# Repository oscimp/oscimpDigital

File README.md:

# oscimpDigital
OscillatorIMP ecosystem originally designed for the digital characterization of ultrastable
oscillators, provides most frontend processing blocks for Software Defined Radio (SDR) reception.

## Motivation

This ecosystem aims at providing a consistent software/hardware, chip independent
(Xilinx Zynq, Altera/Intel Cyclone V soc, ... including the 
[Redpitaya STEMlab 125-14](https://redpitaya.com/stemlab-125-14) and
[Redpitaya SDRlab 122-16](https://www.redpitaya.com/p52/sdrlab-122-16-standard-kit) and
[Redpitaya SIGNALlab 250-12](https://redpitaya.com/signallab-250-12) boards) solution, to assemble and build
designs targeted for FPGA and to generate and cross-compile software, running
on the CPU running embedded GNU/Linux, dedicated to communicate/configure
logic parts. The highlights of oscimpDigital were presented at the [European GNU Radio Days 2019](https://youtu.be/fQgIJl7vu2s), [Maker Space conference](https://www.youtube.com/watch?v=SSzR_pnZnjs&feature=youtu.be) in 2019 and [FOSDEM](https://fosdem.org/2020/schedule/event/fsr_platform_independent_cpu_fpga_co_design/) in 2020.

The assumption underlying all IP block design is a pipelined stream of data 
processed at each clock cycle, with no latencies introduced by FIFOs between blocks.

The tree structure of the project aims at clearly separating the FPGA IPs, Linux kernel modules, userspace libraries 
and documentation:

## Versions

As all opensource software that keeps on evolving, tight API constraints require using specific software versions. We aim at
keeping up to date with latest revisions, so that older versions might/will fail. This set of specifications might help debug failures
to setup OscimpDigital:
* Linux kernel >= 6 MUST be used (GPIO indices starting at 512 and not 906)
* Buildroot >= 2024 MUST be used (REMI web server API)
* Vivado 2019 or 2021 (but 2022.2 is failing at the moment)

## Install

This repository is composed of multiple associated submodules (see sub-READMEs
to see each repository goal). Please refer to the [Wiki](https://github.com/oscimp/oscimpDigital/wiki) for pre-requisites and most significantly Buildroot. Vendor specific tools for synthetizing for the targeted FPGA are also assumed to be functional and accessible through the PATH. A **detailed description** of the installation steps for various boards
is available at [the Wiki page](https://github.com/oscimp/oscimpDigital/wiki). The case of the Redpitaya STEM 125-14 is
detailed at the bottom of the page.

Software versions: OscimpDigital relies on Buildroot and Vivado. The version of Buildroot should not matter much 
*except* for the REMI web server whose API keeps on changing: the latest tested version of Buildroot is 2024.11.1
while earlier versions might rely on the old REMI API.

Vivado 2019 and 2021 are regularly used with OscimpDigital.

### Download

To download this repository and submodules in one command, you need to use
```bash
git clone --recursive https://github.com/oscimp/oscimpDigital.git
```

Or
```bash
git clone https://github.com/oscimp/oscimpDigital.git
cd oscimpDigital
git submodule init
git submodule update
```
to 1/ clone oscimpDigital and 2/ add submodule contents.

### Update

To update repositories you need to use
```bash
git pull
git submodule update
```

## Software environnement

Current Vivado version: 2018.2 to 2019.2

Software parts (applications, libraries and drivers), based on a set of
*Makefile*, uses [buildroot](http://www.buildroot.org) to cross-compiles code.

Thus, you need to download, build and flash your board with a *buildroot*
version configured to your target hardware.

For the specific case of the *Redpitaya* board, not officially supported by
*buildroot*, see
[red_readme](https://github.com/trabucayre/redpitaya/blob/master/README.md)

For the specific case of the *PlutoSDR* board, not officially supported by 
*buildroot*, see [plutosdr_readme](https://github.com/oscimp/PlutoSDR/blob/master/README.md)

## Configuration

The OscillatorIMP ecosystem uses shell environment variables to locate each
repository (*lib*, *fpga_ip*, *linux_driver* and *app*) to allow
In or Out Tree access. In addition to these variables, two other variables are
mandatory to know the target board and the *buildroot* root absolute path for
cross-compilation. 

A sample script (*settings.sh.sample*) is proposed as reference to provide a
complete variable set. You must copy this file and adapt its content to your
specific case, mainly filling the fields:
- *BOARD_NAME*: with the name of your board (*redpitaya*, *redpitaya16*, *plutosdr*, *de0nanosoc* *zedboard* as described in the comment at the beginning of the configuration file). This
variable will be used to determine subdirectories of NFS root, to build designs and run Makefiles accordingly.
- *BR_DIR*: with the absolute path of your *buildroot*. this information is
mandatory to have access to the cross-compiler, linux tree and some other
applications. See above the Software environnement section on how to install buildroot if needed.
- *OSCIMP_DIGITAL_NFS* (optional): when you use *make install* for a Linux driver
or an application, files are copied to a sub-directory of *$OSCIMP_DIGITAL_NFS/$BOARD_NAME*.
By default *OSCIMP_DIGITAL_NFS=/nfs*. Change this variable if you want to
install files in other location.

Once this file has been filled and named *settings.sh*, the command:
```bash
source /somewhere/settings.sh
```
will add these variables to the current environment.

**Warning**: the previous command will add variables only to the current
terminal. To make this setting permanent, the script sourcing must be added
in the user's *~/.bashrc*.

## How it compares with existing solutions ?

Various FPGA design frameworks have been available. Here we list the reasons for pursuing this particular approach of close FPGA/Linux module/GNULinux userspace codesign with respect to other approaches:
- the proprietary approach: of course Xilinx (Vivado) & Altera/Intel (Quartus) provide ready made blackbox solutions to FPGA programming. If you want a vendor-locked solution, these are probably the best alternatives. We want to invest in vendor independent solution that will allow to deploy the framework on any field programmable gate arrays, whether from current (Xilinx/Altera-Intel/Lattice-Microsemi) or future vendors
- Ettus Research has developed RFNOC, an excellent tool for their board but hardly portable to any other platform. A fixed bitstream allows routing packets amongst a fixed set of IPs, as opposed to the proposed approach of a close co-design between the IPs needed for a given design and the associated Linux tools (kernel space and userspace) generated for each new design.
- HLS (High-level Language Synthesis): at the moment most HLS designs require FIFOs and are not compatible with high throughput
streaming data processing, as considered in the radiofrequency data processing for software defined radio
- Migen/Mikymist/ARTIQ (M-Lab)

## [Getting started](https://github.com/oscimp/oscimpDigital/wiki/0Getting-started)

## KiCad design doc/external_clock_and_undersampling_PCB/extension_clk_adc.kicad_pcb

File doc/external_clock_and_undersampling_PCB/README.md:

### PCB for reliable conexion of an external clock and direct connection to ADC inputs for undersampling

Hardware modifications of the 14-bit Red Pitaya (also known as STEMlab 125-14) described
in report.pdf, and the associated KiCAD files (courtesy of Gilles Martin, FEMTO-ST, France,
translated from Eagle) for undersampling by getting rid of the unbalanced-balanced amplifier 
also acting as low pass filter. 

For external clocking (125 MHz), only populate the balun and channel closest to the border of the PCB. The
other two channels are for undersampling by bypassing the unbalanced to balanced differential
amplifiers. Follow
[these instructions](https://redpitaya.readthedocs.io/en/latest/developerGuide/hardware/125-14/top.html#external-125-14)
for wiring modifications (two resistors to be flipped) to disconnect the quartz crystal oscillator
and connect the clock input to the PCLK external source pins.

Replacing the active amplifier with a broadband balun (tested over the whole track-and-hold 
range up to 875 MHz input frequency) requires soldering three tiny wires (differential pair and Vref) 
on each channel at your own risks after removing the inductors connecting the differential 
amplifier output to the ADC inputs. The Vref signal trace must be cut before soldering a 
wire to the via pad whose varnish will have been removed with a sharp blade.

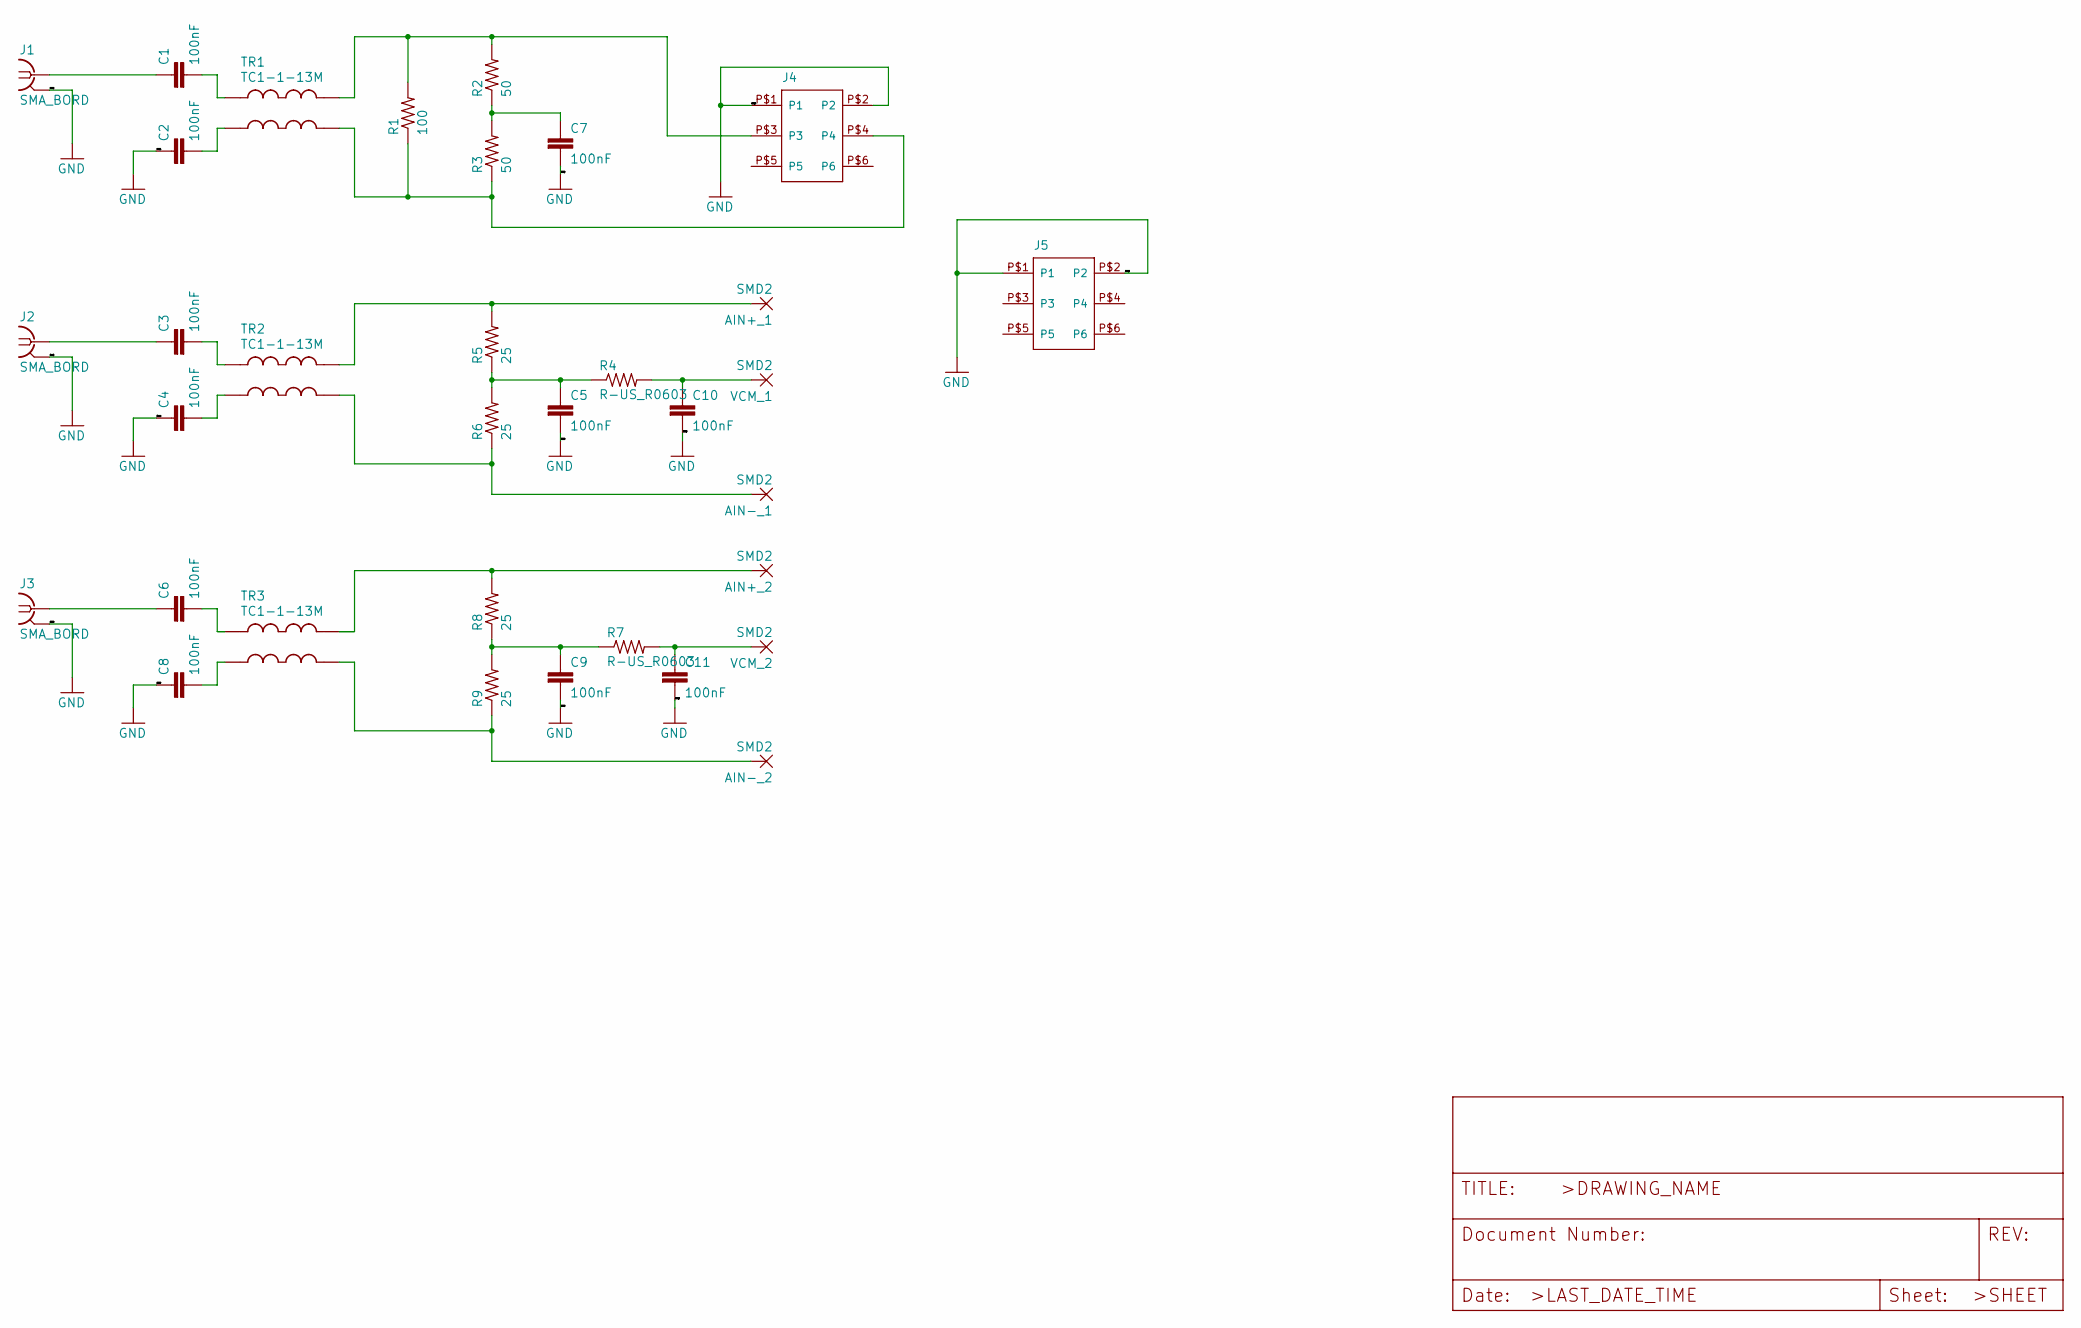
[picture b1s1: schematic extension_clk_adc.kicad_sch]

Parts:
AIN+_1, AIN+_2: SMD2; SMD1,27-2,54
AIN-_1, AIN-_2: SMD2; SMD1,27-2,54
C1, C2, C3, C4, C5, C6, C8, C9, C10, C11: 100nF; C0402
C7: 100nF; C0603
J1, J2, J3: SMA_BORD
J4, J5: DBL_6; DBL6
R1: 100; R0603
R2, R3: 50; R0603
R4, R7: R-US_R0603; R0603
R5, R6, R8, R9: 25; R0603
TR1, TR2, TR3: TC1-1-13M; AT224-1A
VCM_1, VCM_2: SMD2; SMD1,27-2,54

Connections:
GND: C2.1, C4.1, C5.2, C7.2, C8.1, C9.2, C10.2, C11.2, J1.G@1 (2), J1.G@2 (2), J1.G@3 (2), J1.G@4 (2), J2.G@1 (2), J2.G@2 (2), J2.G@3 (2), J2.G@4 (2), J3.G@1 (2), J3.G@2 (2), J3.G@3 (2), J3.G@4 (2), J4.P$1 (P1), J4.P$2 (P2), J5.P$1 (P1), J5.P$2 (P2)
unnamed: AIN+_1.1, R5.2, TR2.P$3 (SEC)
unnamed: AIN+_2.1, R8.2, TR3.P$3 (SEC)
unnamed: AIN-_1.1, R6.1, TR2.P$1 (SEC_DOT)
unnamed: AIN-_2.1, R9.1, TR3.P$1 (SEC_DOT)
unnamed: C1.1, J1.1
unnamed: C1.2, TR1.P$4 (PR)
unnamed: C2.2, TR1.P$6 (PR_DOT)
unnamed: C3.1, J2.1
unnamed: C3.2, TR2.P$4 (PR)
unnamed: C4.2, TR2.P$6 (PR_DOT)
unnamed: C5.1, R4.1, R5.1, R6.2
unnamed: C6.1, J3.1
unnamed: C6.2, TR3.P$4 (PR)
unnamed: C7.1, R2.1, R3.2
unnamed: C8.2, TR3.P$6 (PR_DOT)
unnamed: C9.1, R7.1, R8.1, R9.2
unnamed: C10.1, R4.2, VCM_1.1
unnamed: C11.1, R7.2, VCM_2.1
unnamed: J4.P$3 (P3), R1.2, R2.2, TR1.P$3 (SEC)
unnamed: J4.P$4 (P4), R1.1, R3.1, TR1.P$1 (SEC_DOT)

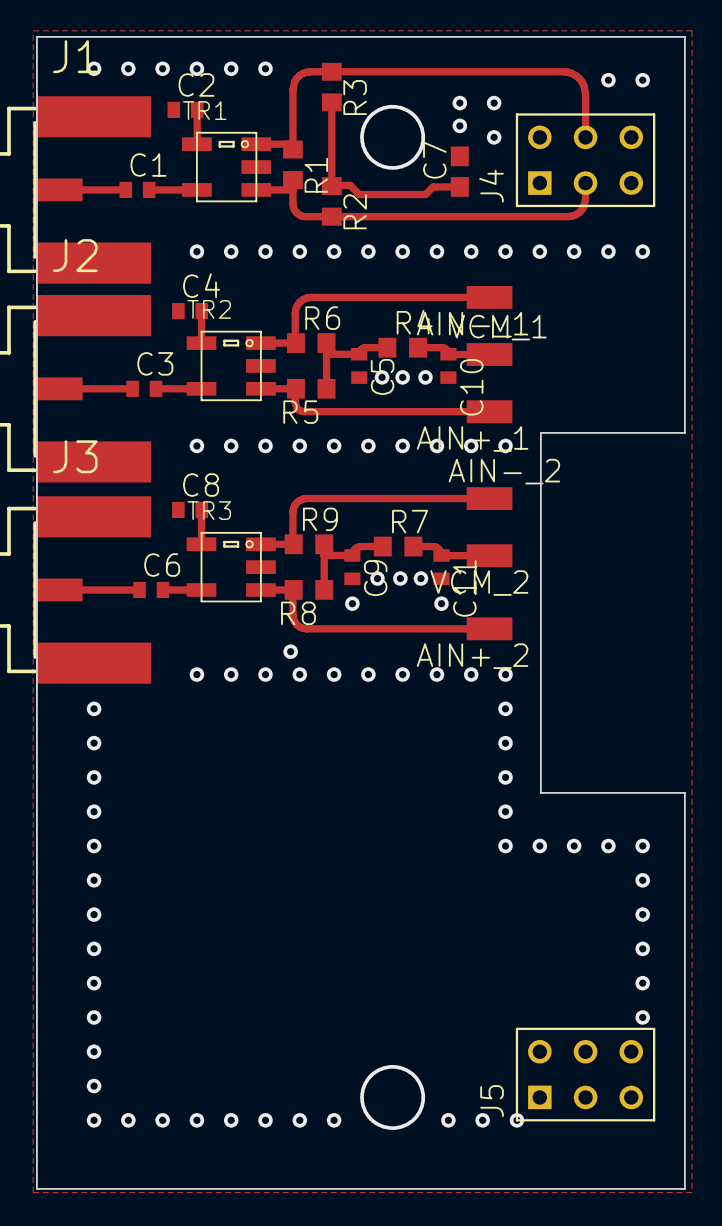
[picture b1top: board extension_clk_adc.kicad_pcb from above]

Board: 2 copper layers, 36.0 x 64.0 mm, 34 parts (0 on the bottom side), 21 nets.

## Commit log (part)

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2019-03-07 update fpga_ip ref: dataComplex, dataReal, nco: improve clock domain communication. dataReal, dataComplex: set axi busy reg high ASAP
2019-03-07 update fpga_ip ref: minor update for nco_counter
2019-03-20 fpga_ip: axiStreamToComplex, axiStreamToReal
2019-03-20 app: module_generator: minor fix
2019-04-01 README
2019-04-02 clock domain error corrected => new datasets and figure
2019-04-02 corrected documentation
2019-04-13 header file
2019-04-19 update linux_driver ref: - add_const to communicate with add_constXX IPs - axi_to_dac to communicate with axi_to_dac
2019-04-19 update lib ref: - add_const: wrapper for add_const_core driver and add_constXX IPs
2019-05-20 update fpga_ip ref: prn: pseudo random number generator xcorr_gps_slow_complex: xcorr between one data stream and one 1bit prn
2019-05-30 update linux_driver ref: fix build for axi_to_dac
2019-06-01 update fpga_ip: new dfu_frm.mk to build flash files out of buildroot
2019-06-04 app: - module_generator: WA for plutosdr - Makefile.inc: add rule to install by ssh
2019-06-06 update fpga_ip ref
2019-06-09 cleanup tutorial3
2019-06-15 doc:tutorials:plutosdr:1-adalmPluto_within_OscimpDigital: add project1 design and app
2019-06-15 update app ref: module_generator minor update
2019-06-15 settings.sh.sample: add details about BOARD_NAME, IP var and ADI_HDL_DIR for plutosdr board
2019-06-16 ignore: add vivado output directory
2019-06-16 update fpga_ip ref: axiStreamToComplex minor update
2019-06-16 doc/tutorials/plutosdr/1-adalmPluto_within_OscimpDigital/project2: TCL based with NCO/demod
2019-06-18 2-PRN_on_PL: update designs
2019-06-18 update app ref: add default design for plutosdr withoscimpDigital support
2019-07-18 doc:IP: add shifter description
2019-07-25 fpga_ip update: new: - shifterReal_dyn,shifterComplex_dyn - redpitaya16 preset - redpitaya_converters - realToAxiStream update: - ip.xml - axi_to_dac
2019-07-25 update lib: new: - utils_conf with shifterXXX_dyn support - axi_to_dac_conf update: - switch,fpgagen: suppress some printf - nco_conf: use 64bits variables and add function to deal with reset accumul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
2019-07-25 update app ref: allows to provides extra files
2019-10-11 doc:IP: add real(complex)ToAxiStream and axiStreamToReal(Complex)
2019-10-16 doc:IP: add documentation about mixerxxx_sin
2019-11-21 slides for the presentation SDR Makerspace (Nov 2019)
2019-11-21 slides
2019-11-24 makerspace: typo
2019-11-29 conference directory
2019-11-29 still conferences ...
2019-11-29 add block assumption
2019-12-19 Redpitaya tutorial: transition to the single ADC/DAC block
2019-12-19 Redpitaya tutorial: transition to the single ADC/DAC block: figure
2019-12-19 Redpitaya tutorial 3: combined ADC/DAC
2019-12-19 Redpitaya tutorial2: xdc full names
2019-12-19 Redpitaya tutorial 2: PDF update
2019-12-19 Redpitaya tutorial2: add shifter between ADC & DAC in case of 16-bit Redpitaya
2019-12-23 Update axi_to_dac.md
    axi_to_dac example: syntax errors
2019-12-23 Redpitaya tutorial 2: correct screenshot for part selection
2019-12-30 Update README.md
    video Makerspace
2020-01-06 Redpitaya tutorial corrections
2020-01-07 Update fpga_ip ref: - new makefile structure with a top generic top makefile and sub .mk used to support commercial tools; - TCL script to provides vendor abstraction layer for design assembly
2020-01-08 fpga_ip: small modification in gen_module_generator_xml
2020-01-08 fpga_ip: minor fix in gen_module_generator_xml
2020-01-08 Revert "doc:IP: axi_to_dac: typo in register REG_DATAB"
    This reverts commit 148972dcdde75082e37f1bfdab2f812007278620.
2020-01-08 tutorials:redpitaya:4-PLPS: update tcl to use redpitaya_converters, add support for redpitaya16 and everything around xml to use current module_generator file content
2020-01-08 tutorials:redpitaya:2-PL: uses redpitaya_converters and add redpitaya16 support
2020-01-09 IP:mixer*
2020-01-11 doc/IP: switch
2020-01-12 doc/IP: data_to_RAM
2020-01-12 doc/redpitaya/4-FIR: FIR tutorial including oscilloscope observation of filtered output
2020-01-12 fpga_ip
2020-01-14 update fpga_ip: - update README - fix boards.def (typo for redpitaya16) - fix FREQ_HZ for redpitaya_converters/clk_o
2020-01-15 doc:tutorials:redpitaya:4-FIR: update design
2020-01-22 update fpga_ip: fix in nco_counter
2020-01-23 update fpga_ip - use coherent parameters name for meanXX - syncTrigStream: produces data stream only on a trigger event - dataComplex_dma_direct: use CPU RAM to store an complex data stream
2020-01-23 doc/IP/nco_counter correction
2020-01-24 update fpga_ip: meanReal small typo
2020-01-24 redpitaya/4-FIR: figure updates
2020-01-27 doc/redpitaya/4-FIR: PDF
2020-01-28 fpga_ip: introduce print_businterfaces: a tools to display IP details
2020-02-03 update fpga_ip
2020-02-05 doc:tutorials:plutosdr:2-PRN_on_PL: prn -> prnGenerator
2020-02-11 doc:tutorials:plutosdr: fix some IP names or parameters
2020-02-13 fpga_ip: minor fix
2020-02-16 Update README.md
    FOSDEM
2020-02-16 cleanup for wiki page
2020-02-16 figure pour wiki
2020-02-18 doc/tutorials/redpitaya/3: be more coherent
2020-02-18 doc/tutorials/redpitaya/4: add missing figure
2020-02-19 settings.sh: add LANG for Vivado to work on French computers
2020-02-27 app with Redpitaya balun circuit
2020-03-03 fpga_ip: ip.xml update
2020-03-03 introduce dupplReal and dupplComplex
2020-03-10 initial draft for TCL tutorial
2020-03-11 Update settings.sh.sample
    board names in settings.sh configuration file
2020-03-11 Update settings.sh.sample
    add PATH to access tools in app (module_generator) and fpga_ip (python script describing IP interfaces)
2020-03-20 update fpga_ip ref: - add pidv3_axi IP - update and fix pwm_axi
2020-03-27 fix app hash
2020-04-21 Create README.md
    documentation creation
2020-04-21 linux_driver: README on how to compile module
2020-04-24 2PL: figure path update
2020-04-24 3-PLPS: README & figure
2020-04-24 3-PLPS: missing figure
2020-04-24 4-FIR: figures
2020-04-24 5-NCO: README & figures
2020-04-24 6_TCL: README & figures
2020-05-09 README.md of webserver_generator
2020-05-09 Tutorial for a first setup with RedPitaya STEM 125-14
2020-05-15 Update main.cpp
    typo
2020-05-15 Doc: move getting started to doc
2020-05-30 add missing pidv3_axi_conf.* files
2020-06-19 move getting started doc associated install* images to doc folder
2020-06-23 Update README.md
    Update to README after merging Redpitaya introductory tutorial with Wiki pages.
2020-06-23 doc/IP: typo
2020-06-24 doc/tutorials/redpitaya/2-PL: resize first fig
2020-06-26 Update axi_to_dac.md
    testing from shell (devmem)
2020-06-30 Update README.md
    Wiki URL
2020-09-27 add example and board name for redpitaya12
2020-09-28 move figure
2020-09-28 webserver_generator update
2020-09-29 declaration of interrupt in dataReal_to_ram
2020-09-29 fpga_ip/dataReal_to_ram: minor fix
2020-09-29 zedboard support
2020-10-02 update redpitaya12 example and IP naming
2020-10-05 update description for redpitaya_converters_12
2020-10-09 example design double_iq_pid_vco for redpitaya12
2020-10-12 fix data_to_ram driver
2020-10-19 Buttons for redpidaya_converters_12 commutators in webserver_generator
2020-10-20 rm useless comments in ip redpitaya_converters_12
2020-10-20 update redpitaya_converters_12 doc
2020-10-20 webserver_generator small errors correction
2020-10-28 redpitaya_converters_12 correct DAC output sign
2020-12-10 Update README.md
    readme: url of conferences describing OscimpDigital
2021-01-06 fpga_ip: small Makefiles update
2021-01-11 app: redpitaya16 support for redpitaya/adcChanADmaDirect
2021-01-11 update app
2021-01-15 fpga_ip: magnitude, cplx_conj
2021-01-19 app/redpitaya/double_iq_pid_vco: redpitaya16 compatibility: WIP
2021-01-27 app: redpitaya/double_iq_pid_vco: WIP
2021-01-28 double_iq_pid_vco diagram
2021-01-29 screenshot
2021-01-29 replace string with boolean, slider callback function with onchange.do, remove UTF8 encoding
2021-02-02 liboscimp_fpga.py correction on get_values
2021-02-04 doc/tutorials/redpitaya/3-PLPS: fix module_generator path
2021-02-04 app:module_generator: more check
2021-02-12 fpga_ip: vivado typo
2021-02-18 lib/pidv3_axi_conf: typo
2021-03-03 Update README.md
    correction and minor changes of the tutorial
2021-03-05 16bit redpitaya procedure paragraph moved up
    the procedure to adapt the code for redpitaya 16 was located at the bottom of the tuto. Now it is located in the connecting blocks to the FPGA so that people will be aware that they can't use the sam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
2021-03-05 adding one step to configure the program for RP16
    to make the program work under redpitaya16, one must check that the redpitaya IP is correctly configured
2021-03-05 Correction amelioration
    more details on some sections
2021-03-05 added comment in the octave program
2021-03-09 pidv3 setpoint is working now
2021-03-18 correction of a minor error
2021-04-02 minor change
2021-04-06 amelioration and correction
2021-04-12 app: tools/webserver_generator: add missing shifterComplex_dyn
2021-04-13 lib: typo
2021-04-14 doc/IP/figures: pidv3 RTL diagram
2021-04-16 fpga_ip: add_const: fix
2021-04-30 fpga_ip: new IP: delayTempoReal_axi
2021-04-30 lib: add delayTempo support
2021-05-03 fpga_ip: new cordicAtan IP
2021-05-11 fix fpga_ip ref'
2021-05-12 fpga_ip/mixerXXX_sin: allows to select primary stream
2021-05-18 add fft ip/lib/driver
2021-05-18 fft in ip.xmp + readme update
2021-05-19 delayTempoReal_axi in webserver_generator
2021-05-28 add window IP
2021-05-28 fpga_ip/README.md + liboscimp_fpga.py
2021-05-28 update fpga_ip/README.md again
2021-06-11 autorun_generator -> be lazy + webserver_generator switchComplex
2021-06-11 add autorun_generator readme
2021-07-02 doc:ip:windowReal: minor corrections
2021-07-14 update window and fft doc
2021-07-15 fft doc with the figure is better
2021-07-15 update app ref
2021-07-16 update readme autorun_generator
2021-07-26 nco in webserver_fenerator: fix float load error
2021-09-07 fpga_ip: fix pidv3 with out size gt internal size
2021-09-08 fpga_ip: nco_counter fix
2021-11-19 update double_iq_pid_vco
2022-03-18 added documentation images for dynamic shifter, iir_lpf_real. For unwrap_phase_diff- after adding the synchronization registers improving the timing performance during Vivado synthesis
2022-03-18 description of IIR lowpass filter
2022-03-31 cropped borders
2022-05-05 fix webserver and remi checkbox value and pluto dfu flash routine
2022-05-05 switch: default to False (as IP)
2022-06-29 fix tab
2022-09-07 now can joint max7311 with both SignalLab v1.1 and v1.2
2022-09-07 rm useless lines
2022-11-21 update lib ref (scp protocol)
2022-11-25 doc/IP: magnitude
2022-11-25 update fpga_ip ref: magnitude and add_const update
2022-11-28 fpga_ip: update ref (firXXX)
2022-11-28 partial FIR documentation
2022-11-28 doc/IP: add_const IP
2022-11-29 doc/IP/figures/shifter2: add white bg
2022-11-29 doc/IP/shifter: dyn complement
2022-12-01 doc/IP/mixer_multiplier
2022-12-05 referesh fpga_ip (add_const), update add_const doc about saturation
2022-12-05 doc/IP/add_const: typo
2023-03-24 doc: lutGenerator, update fpga_ip, lib, linux_driver refs
2023-07-07 sampleCounterXX: IP to associate counter to samples
2023-11-13 2-PL.pdf
2023-11-15 * fpga_ip 9f0a34f...2b3ea56 (1): > nco_counter: trigger_o length is configurable, add a saw tooth output
2024-03-09 * app 749c94c...cba8475 (1): > redpitaya125-14: design example for the dataComplex2ram and dataComplex2ram_pingpong
    * fpga_ip 2b3ea56...a8477c6 (3):
    > ip: specify drivers to use
    > ram_to_dataReal: new IP
    > dataComplex_to_ram_pingpong: new IP
    * linux_driver a08807c...3a483a6 (1):
    > data_to_ram_core: increase timeout
2024-07-18 add documentation according to Jack
2024-11-01 PCB for ext clock and undersampling
2024-11-30 * app 4e6c005...9b695d0 (1): > redpitaya: dataReal2ram_pingpong example
    * fpga_ip 24fd8e9...a93778a (2):
    > dataReal_to_ram_pingpong: fix even/odd//pin/pong mechanism
    > Merge branch 'dev_dataReal_to_ram_pingpong'
2025-01-24 add triangle wave at NCO counter output
2025-03-19 add tools/app/ to path
2025-03-19 recent app
2025-06-16 screenshots double_iq_pid_vco
2025-06-18 notes on PID
2025-07-14 * fpga_ip 89dc0d2...3e6c208 (1): > enableExtenderXX: new IP to extend either enable or EOF signals
2025-12-02 update documentation
2025-12-02 update tutorial FIR
2025-12-02 linux_driver: refresh
2025-12-03 update fpga_ip version
